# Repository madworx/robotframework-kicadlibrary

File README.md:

# robotframework-kicadlibrary

A [Robot Framework](http://robotframework.org/) library for validating [KiCad](http://kicad.org/) designs.

Releases are available via regular [PyPI](https://pypi.org/project/robotframework-kicadlibrary/) as well as [GitHib releases](https://github.com/madworx/robotframework-kicadlibrary/releases). Example projects/usage is available under the `examples/` sub-directory.

[Keyword documentation](https://madworx.github.io/robotframework-kicadlibrary/KiCadLibrary.html) is available online, as well as downloadable via [GitHub Releases](https://github.com/madworx/robotframework-kicadlibrary/releases/latest).

## Getting Started

### Prerequisites

You'll need an installation of Python, as well as `pip` and a working
installation of KiCad. Please consult your operating system
documentation on how to install these tools.

You will also need Robot Framework installed, but if you're installing
using `pip`, Robot Framework will automatically be installed for you.

### Installing KiCad, PIP and the library

This is dependent on your local operating system, but if you'te running
any form of Unix-clone, it should typically be something in the lines of:

```
# Debian based systems
$ sudo apt-get install python-pip kicad
$ sudo pip install robotframework-kicadlibrary

# RedHat based systems:
$ sudo yum -y install epel-release
$ sudo yum -y install python-pip kicad
$ sudo pip install robotframework-kicadlibrary
```

### Installing using PIP with existing environment

```
$ pip install robotframework-kicadlibrary
```

## Using the library

```
*** Variables ***
Library    KiCadLibrary    schema=myproject.sch    pcb=myproject.kicad_pcb

*** Test cases ***
Module pads should be on grid
    Module Pads Should Be On Grid    50 mil    reference=.*$
```

## Contributing

Any and all contributions are welcome, in the form of [pull requests](https://github.com/madworx/robotframework-kicadlibrary/pulls).

## Versioning

We use [SemVer](http://semver.org/) for versioning. For the versions available, see the [releases on this repository](https://github.com/madworx/robotframework-kicadlibrary/releases).

## Authors

* **Martin Kjellstrand** - *Initial work* - [madworx](https://github.com/madworx)

## License

This project is licensed under the MIT License - see the [LICENSE.txt](LICENSE.txt) file for details

## Developer information / Preparing a release

To create a release please follow this outline:

* Do your development work in a separate branch.
* Write unit-tests (`tests/`) and/or integration tests (`examples/`) for your code.
* Once all local tests validate, and you have 100% code coverage, push to GitHub.

### If you have commit access to the main repository

* Once build hooks at Github/Sonarcloud/pyup etc have completed, tag a pre-release (`x.y.zrc0`)
* If that build completes, perform a PR into `master`, squashing the commit history.
* Tag the `master` branch with the new release version, ahdering to semantic versioning.
* Remove any `pre` artifacts from Docker Hub and PyPI.
* Delete the `rc*` tags from the repository.
  `git tag -d x.y.zrcN`, followed by `git push origin :x.y.zpreN`.

### If you don't have commit access to the main repository

* Submit a PR towards the `master` branch of the [main repository](https://github.com/madworx/robotframework-kicadlibrary/).

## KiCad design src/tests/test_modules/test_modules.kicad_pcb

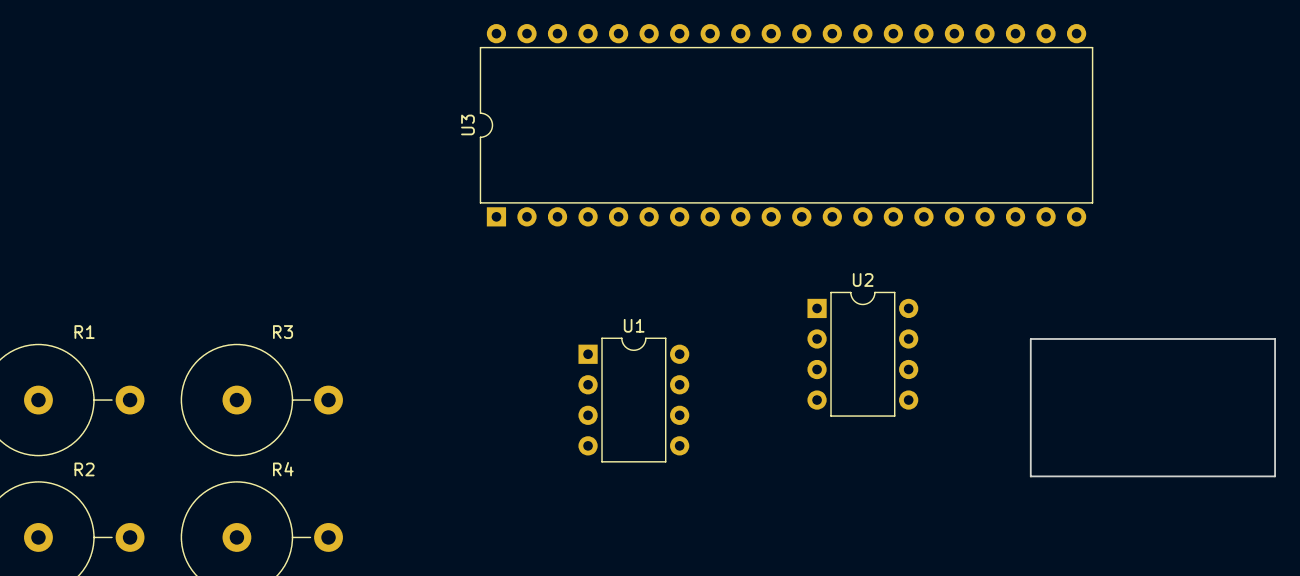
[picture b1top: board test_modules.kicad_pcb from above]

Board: 2 copper layers, 7 parts (0 on the bottom side), 8 nets, no tracks yet.

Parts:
R1: 10k; R_Axial_DIN0922_L20.0mm_D9.0mm_P7.62mm_Vertical
R2: 330; R_Axial_DIN0922_L20.0mm_D9.0mm_P7.62mm_Vertical
R3: 2 M; R_Axial_DIN0922_L20.0mm_D9.0mm_P7.62mm_Vertical
R4: 0.1uF; R_Axial_DIN0922_L20.0mm_D9.0mm_P7.62mm_Vertical
U1, U2: NA555P; DIP-8_W7.62mm
U3: 8255; DIP-40_W15.24mm

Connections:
/CV: U1.5, U2.5
/DIS: U1.7, U2.7
/Q: U1.3, U2.3
/THR: U1.6, U2.6
/TR: U1.2, U2.2
/~R: U1.4, U2.4
GND: U1.1, U2.1
VCC: U1.8, U2.8

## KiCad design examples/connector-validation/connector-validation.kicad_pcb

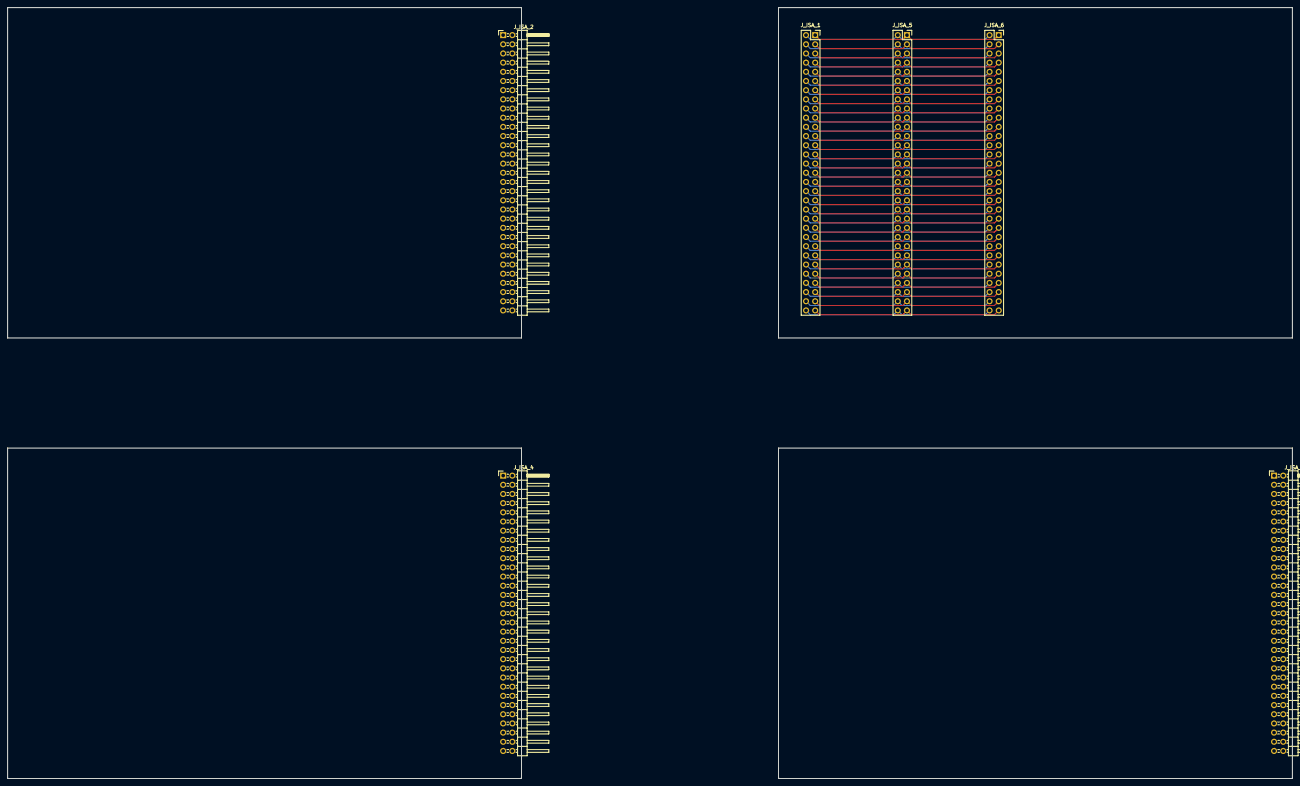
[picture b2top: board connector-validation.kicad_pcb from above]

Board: 2 copper layers, 355.6 x 213.4 mm, 6 parts (0 on the bottom side), 67 nets.

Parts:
J_ISA_1, J_ISA_5, J_ISA_6: Conn_02x31_Counter_Clockwise; PinSocket_2x31_P2.54mm_Vertical
J_ISA_2, J_ISA_3, J_ISA_4: Conn_02x31_Counter_Clockwise; PinHeader_2x31_P2.54mm_Horizontal

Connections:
/backplane/+12V: J_ISA_1.9, J_ISA_5.9, J_ISA_6.9
/backplane/-5V: J_ISA_1.5, J_ISA_5.5, J_ISA_6.5
/backplane/-12V: J_ISA_1.7, J_ISA_5.7, J_ISA_6.7
/backplane/AEN: J_ISA_1.52, J_ISA_5.52, J_ISA_6.52
/backplane/ALE: J_ISA_1.28, J_ISA_5.28, J_ISA_6.28
/backplane/BA00: J_ISA_1.32, J_ISA_5.32, J_ISA_6.32
/backplane/BA01: J_ISA_1.33, J_ISA_5.33, J_ISA_6.33
/backplane/BA02: J_ISA_1.34, J_ISA_5.34, J_ISA_6.34
/backplane/BA03: J_ISA_1.35, J_ISA_5.35, J_ISA_6.35
/backplane/BA04: J_ISA_1.36, J_ISA_5.36, J_ISA_6.36
/backplane/BA05: J_ISA_1.37, J_ISA_5.37, J_ISA_6.37
/backplane/BA06: J_ISA_1.38, J_ISA_5.38, J_ISA_6.38
/backplane/BA07: J_ISA_1.39, J_ISA_5.39, J_ISA_6.39
/backplane/BA08: J_ISA_1.40, J_ISA_5.40, J_ISA_6.40
/backplane/BA09: J_ISA_1.41, J_ISA_5.41, J_ISA_6.41
/backplane/BA10: J_ISA_1.42, J_ISA_5.42, J_ISA_6.42
/backplane/BA11: J_ISA_1.43, J_ISA_5.43, J_ISA_6.43
/backplane/BA12: J_ISA_1.44, J_ISA_5.44, J_ISA_6.44
/backplane/BA13: J_ISA_1.45, J_ISA_5.45, J_ISA_6.45
/backplane/BA14: J_ISA_1.46, J_ISA_5.46, J_ISA_6.46
/backplane/BA15: J_ISA_1.47, J_ISA_5.47, J_ISA_6.47
/backplane/BA16: J_ISA_1.48, J_ISA_5.48, J_ISA_6.48
/backplane/BA17: J_ISA_1.49, J_ISA_5.49, J_ISA_6.49
/backplane/BA18: J_ISA_1.50, J_ISA_5.50, J_ISA_6.50
/backplane/BA19: J_ISA_1.51, J_ISA_5.51, J_ISA_6.51
/backplane/CLK: J_ISA_1.20, J_ISA_5.20, J_ISA_6.20
/backplane/DB0: J_ISA_1.54, J_ISA_5.54, J_ISA_6.54
/backplane/DB1: J_ISA_1.55, J_ISA_5.55, J_ISA_6.55
/backplane/DB2: J_ISA_1.56, J_ISA_5.56, J_ISA_6.56
/backplane/DB3: J_ISA_1.57, J_ISA_5.57, J_ISA_6.57
/backplane/DB4: J_ISA_1.58, J_ISA_5.58, J_ISA_6.58
/backplane/DB5: J_ISA_1.59, J_ISA_5.59, J_ISA_6.59
/backplane/DB6: J_ISA_1.60, J_ISA_5.60, J_ISA_6.60
/backplane/DB7: J_ISA_1.61, J_ISA_5.61, J_ISA_6.61
/backplane/DRQ1: J_ISA_1.18, J_ISA_5.18, J_ISA_6.18
/backplane/DRQ2: J_ISA_1.6, J_ISA_5.6, J_ISA_6.6
/backplane/DRQ3: J_ISA_1.16, J_ISA_5.16, J_ISA_6.16
/backplane/GND: J_ISA_1.1, J_ISA_1.10, J_ISA_1.31, J_ISA_5.1, J_ISA_5.10, J_ISA_5.31, J_ISA_6.1, J_ISA_6.10, J_ISA_6.31
/backplane/INQ2: J_ISA_1.4, J_ISA_5.4, J_ISA_6.4
/backplane/IO: J_ISA_1.62, J_ISA_5.62, J_ISA_6.62
/backplane/IO_READY: J_ISA_1.53, J_ISA_5.53, J_ISA_6.53
/backplane/IRQ3: J_ISA_1.25, J_ISA_5.25, J_ISA_6.25
/backplane/IRQ4: J_ISA_1.24, J_ISA_5.24, J_ISA_6.24
/backplane/IRQ5: J_ISA_1.23, J_ISA_5.23, J_ISA_6.23
/backplane/IRQ6: J_ISA_1.22, J_ISA_5.22, J_ISA_6.22
/backplane/IRQ7: J_ISA_1.21, J_ISA_5.21, J_ISA_6.21
/backplane/OSC: J_ISA_1.30, J_ISA_5.30, J_ISA_6.30
/backplane/RESET: J_ISA_1.2, J_ISA_5.2, J_ISA_6.2
/backplane/TC: J_ISA_1.27, J_ISA_5.27, J_ISA_6.27
/backplane/UNUSED: J_ISA_1.8, J_ISA_5.8, J_ISA_6.8
/backplane/VCC: J_ISA_1.3, J_ISA_1.29, J_ISA_5.3, J_ISA_5.29, J_ISA_6.3, J_ISA_6.29
/backplane/~DACK0: J_ISA_1.19, J_ISA_5.19, J_ISA_6.19
/backplane/~DACK1: J_ISA_1.17, J_ISA_5.17, J_ISA_6.17
/backplane/~DACK2: J_ISA_1.26, J_ISA_5.26, J_ISA_6.26
/backplane/~DACK3: J_ISA_1.15, J_ISA_5.15, J_ISA_6.15
/backplane/~IOR: J_ISA_1.14, J_ISA_5.14, J_ISA_6.14
/backplane/~IOW: J_ISA_1.13, J_ISA_5.13, J_ISA_6.13
/backplane/~MEM: J_ISA_1.11, J_ISA_1.12, J_ISA_5.11, J_ISA_5.12, J_ISA_6.11, J_ISA_6.12
/graphics/GND: J_ISA_2.1, J_ISA_2.10, J_ISA_2.31
/graphics/VCC: J_ISA_2.3, J_ISA_2.29
/graphics/~MEM: J_ISA_2.11, J_ISA_2.12
/sound/GND: J_ISA_4.1, J_ISA_4.10, J_ISA_4.31
/sound/VCC: J_ISA_4.3, J_ISA_4.29
/sound/~MEM: J_ISA_4.11, J_ISA_4.12
/storage/GND: J_ISA_3.1, J_ISA_3.10, J_ISA_3.31
/storage/VCC: J_ISA_3.3, J_ISA_3.29
/storage/~MEM: J_ISA_3.11, J_ISA_3.12

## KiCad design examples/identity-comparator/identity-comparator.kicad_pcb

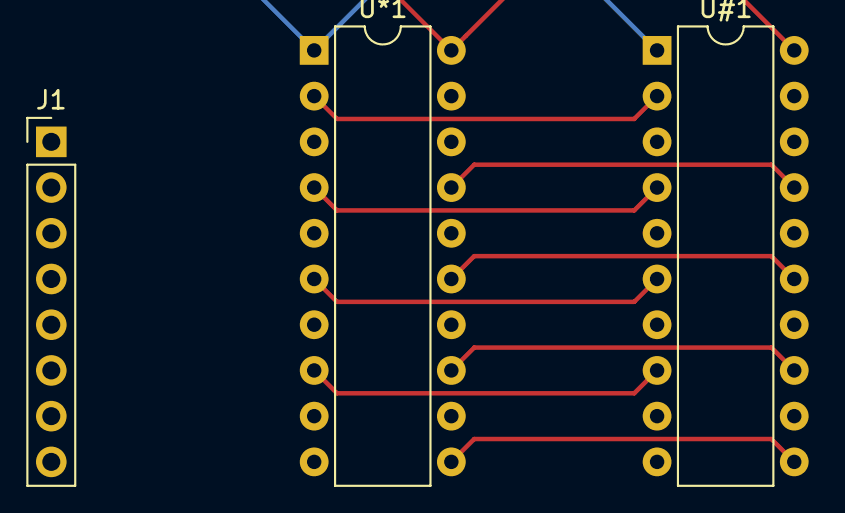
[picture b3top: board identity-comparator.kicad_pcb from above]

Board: 2 copper layers, 3 parts (0 on the bottom side), 10 nets.

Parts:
J1: Conn_01x08; PinHeader_1x08_P2.54mm_Vertical
U#1: 74LS688; DIP-20_W7.62mm
U*1: 74LS688; DIP-20_W7.62mm

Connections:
/d0: J1.1, U#1.2, U*1.2
/d1: J1.2, U#1.4, U*1.4
/d2: J1.3, U#1.6, U*1.6
/d3: J1.4, U#1.8, U*1.8
/d4: J1.5, U#1.11, U*1.11
/d5: J1.6, U#1.13, U*1.13
/d6: J1.7, U#1.15, U*1.15
/d7: J1.8, U#1.17, U*1.17
GND: U#1.1, U#1.3, U#1.5, U#1.9, U#1.10, U#1.14, U#1.18, U*1.1, U*1.3, U*1.5, U*1.9, U*1.10, U*1.14, U*1.18
VCC: U#1.7, U#1.12, U#1.16, U#1.20, U*1.7, U*1.12, U*1.16, U*1.20

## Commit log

2018-12-08 Initial import.
2018-12-10 Transtion to using madworx/kicad-library-utils.
2018-12-10 Add .travis.yml.
2018-12-11 Enable building with Travis and upload artifacts to GitHub releases.
2018-12-11 Integrate Travis CI (#1)
    * Add .travis.yml.
    * Enable building with Travis and upload artifacts to GitHub releases.
2018-12-11 Draft of Sonarcloud integration.
2018-12-11 Exclude kicad_library_utils from analysis. (Not-invented-here) Add coverage reporting.
2018-12-11 Add both coverage and test results XML to sonarcloud invocation.
2018-12-11 Fix exclusion syntax for dirs.
2018-12-11 Corrected --cov argument.
2018-12-11 Add Sonarcloud integration. (#2)
    * Draft of Sonarcloud integration.
    * Exclude kicad_library_utils from analysis. (Not-invented-here)
    * Add coverage reporting.
    * Add both coverage and test results XML to sonarcloud invocation.
    * Corrected --cov argument.
2018-12-11 Tighten up Sonarcloud exclusions.
2018-12-11 Add README.md. Clean up a few sonarqube smells.
2018-12-11 Does travis support multiple deployments?
2018-12-11 Syntax correction for Travis CI multipled deployments.
2018-12-11 Syntax correction.
2018-12-11 Add link to PyPI in README.md
2018-12-11 ... as well as badge.
2018-12-11 (w/ space)
2018-12-11 Add support for releasing to PyPI (#3)
    * Add link and for PyPI in README.md
2018-12-11 Tag Sonar invocations with release version if we're even with a tag.
2018-12-11 Corrected Sonar variable name.
2018-12-11 Include README.md as Python package description. Replace "find_packages" with hard-coded list. (Stop adding internal resources to the distribution) Depend on RF <= 3.1 instead of <= 3.0.4 since the l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
2018-12-12 Improved test coverage.
2018-12-14 Improved documentation plus link to Keyword documentation.
2018-12-14 Add first example project; Validating identity comparators.
2018-12-14 Added more documentation to README.md. Added license. Added classifiers to the Python package.
2018-12-14 More docuemntational fixes.
2018-12-14 Add examples and documentation (#4)
    * Add first example project; Validating identity comparators.
    * Added more documentation to README.md.
    * Added license.
    * Added classifiers to the Python package.
2018-12-14 First grab at improving test coverage (#5)
    * Improved test coverage.
    * Improved documentation plus a link to Keyword documentation.
2018-12-14 Fixed a glitch in the matrix.
2018-12-16 Add code of conduct documentation
2018-12-16 Initial import of dockerization.
2018-12-16 Also remember to actually build the image ;-)
2018-12-16 Attempt to fix docker hub deployment.
2018-12-16 setuptools_scm isn't included in travis by default.
2018-12-16 Dockerization test release.
2018-12-16 Fix.
2018-12-16 Fix version on docker-extract-artifacts.
2018-12-16 More fixes for dockerization release deployment.
2018-12-16 More bash fixes for Travis CI script deployment.
2018-12-16 Travis workarounds.
2018-12-16 Test.
2018-12-16 More Travis work-arounds.
2018-12-16 Add dockerized build & deployment to Docker Hub. (#6)
    * Initial import of dockerization.
    * setuptools_scm isn't included in travis by default.
2018-12-16 Reinstate SonarCloud code coverage statistics.
2018-12-16 Pathfixes.
2018-12-16 Make PyPI releases work properly.
2018-12-16 Remove .html from PyPI deployment.
2018-12-16 PyPI fixes.
2018-12-17 Improve test coverage by including integration tests (examples/) into test suite. Ensure that relative file names are properly resolved.
2018-12-17 Quiet down apt a bit.
2018-12-17 Quiet down apt even further.
2018-12-17 Quiet down even further.
2018-12-17 Include version number in generated documentation filename.
2018-12-17 Add example/integration test for subsheets.
2018-12-17 If building inside Docker environment, use KICADLIBRARY_VERSION variable instead of setuptools_scm.
2018-12-17 Preparing for 1.0.0 release (#7)
    * Improve test coverage by including integration tests (examples/) into test suite.
    Ensure that relative file names are properly resolved.
    * Quiet down apt.
    * Include version number in generated documentation filename.
    * Add example/integration test for subsheets.
    * If building documentation inside Docker environment, use KICADLIBRARY_VERSION variable
2018-12-18 Test deploying documentation to github pages.
2018-12-18 Ensure that the script terminates if cd-ci-glue returns an error.
2018-12-18 Export GH_TOKEN to deployment script.
2018-12-18 Enable detailed debugging.
2018-12-18 Automated documentation update
2018-12-18 Hopefully final version before pushing official 1.0.1 release.
2018-12-18 Updated link to Keyword documentation in README.md.
2018-12-18 Deploy documentation to GitHub Pages (#8)
    * Deploy generated documentation to GitHub Pages.
    * Updated link to Keyword documentation in README.md.
2018-12-18 Remove obsolete fixme from library.
2018-12-18 Add docker labels.
2018-12-18 Add Docker image status to badge list.
2018-12-18 Tag published Docker images as latest.
2018-12-18 Include version in generated keyword documentation. Added links to library documentation, as well as README.md.
2018-12-18 Add more badges to README.md dashboard.
2018-12-18 Updated "front page".
2018-12-19 Upped test coverage to near 100%.
2018-12-19 Upped test coverage to near 100%. (#10)
2018-12-19 Further improved test-coverage. Decorated README.md. Keep integrations tests from dropping result files.
2018-12-19 Added better example. Reinstated deprecated keyword into working order.
2018-12-19 Documentation improvements.
2018-12-19 Linting fixes.
2018-12-19 Implicit repo is implicit.
2018-12-22 Minor documentational fixes.
2018-12-27 Added `Complement Modules By Reference keyword`. Improved documentation.
2018-12-27 Changed wording in developer documentation.
2018-12-27 Add new keywords (#11)
    Added new keywords:
    `Modules Should Have Values Matching` - validate that selected modules have valid values.
    `Complement Modules By Reference` - perform set complement operation on module lists.
2018-12-27 Updated/Improved documentation.
2018-12-29 Omit __main__.py from coverage reports.
2019-04-16 Library now builds and works on both Python 2.7 and 3.7. (But still being built inside docker container) Both Py3 compatability fixes in the code, as well as in the infrastructure parts. (Makefile, .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
2019-06-21 Use "skip_existing" to prevent Travis to attempt to push sources twice to PyPI
2020-09-12 Adapt to newer versions of Robot Framework and KiCad, updating FOR loop syntax as well as deprecating LM555. Ensure Python3 is used. Stop building for Python 2.7 Fix code smell (is not -> !=). Update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
2020-09-12 Initial draft of new keyword to validate that all modules have all their pads connected to a valid net.
2020-09-12 Python code formatting fixes for test-cases.
2020-09-12 Try upgrading to xunit2 syntax.
2020-09-12 Temporarily disable pylint validatations to get proper feedback from Soundcloud.
2020-09-12 Add missing testcase for new logic.
2020-09-12 Update .gitignore to reflect reality.
2020-09-12 Further remove Python2 compat
2020-09-13 Try disabling the junit_family setting.
2020-09-13 Try to get SonarCloud coverage reports working again.
2020-09-13 Get SonarCloud coverage reports working again.
2020-09-14 See if we get test cases listed on SC.
2020-09-14 Adjustments for new SonarCloud properties.
2020-09-16 Disable warnings from SonarCloud regarding shallow clone.
2020-09-16 Add stub testing of actual keyword.
2021-03-12 Update robotframework requirement from <4 to <5
    Updates the requirements on [robotframework](https://github.com/robotframework/robotframework) to permit the latest version.
    - [Release notes](https://github.com/robotframework/robotframework/releases)
    - [Commits](https://github.com/robotframework/robotframework/compare/2.0...v4.0)
2021-04-29 Upgrade to GitHub-native Dependabot
2021-07-21 Upgrade to GitHub-native Dependabot (#16)
2021-11-10 Update README.md
    https://forum.kicad.info/t/warning-avoid-all-links-to-kicad-pcb-org-use-kicad-org/31521
2022-03-24 Update robotframework requirement from <4 to <6
    Updates the requirements on [robotframework](https://github.com/robotframework/robotframework) to permit the latest version.
    - [Release notes](https://github.com/robotframework/robotframework/releases)
    - [Commits](https://github.com/robotframework/robotframework/compare/2.0...v5.0)
    ---
    updated-dependencies:
    - dependency-name: robotframework
2022-10-20 Update robotframework requirement from <4 to <7
    Updates the requirements on [robotframework](https://github.com/robotframework/robotframework) to permit the latest version.
    - [Release notes](https://github.com/robotframework/robotframework/releases)
    - [Commits](https://github.com/robotframework/robotframework/compare/2.0...v6.0)
    ---
    updated-dependencies:
    - dependency-name: robotframework
